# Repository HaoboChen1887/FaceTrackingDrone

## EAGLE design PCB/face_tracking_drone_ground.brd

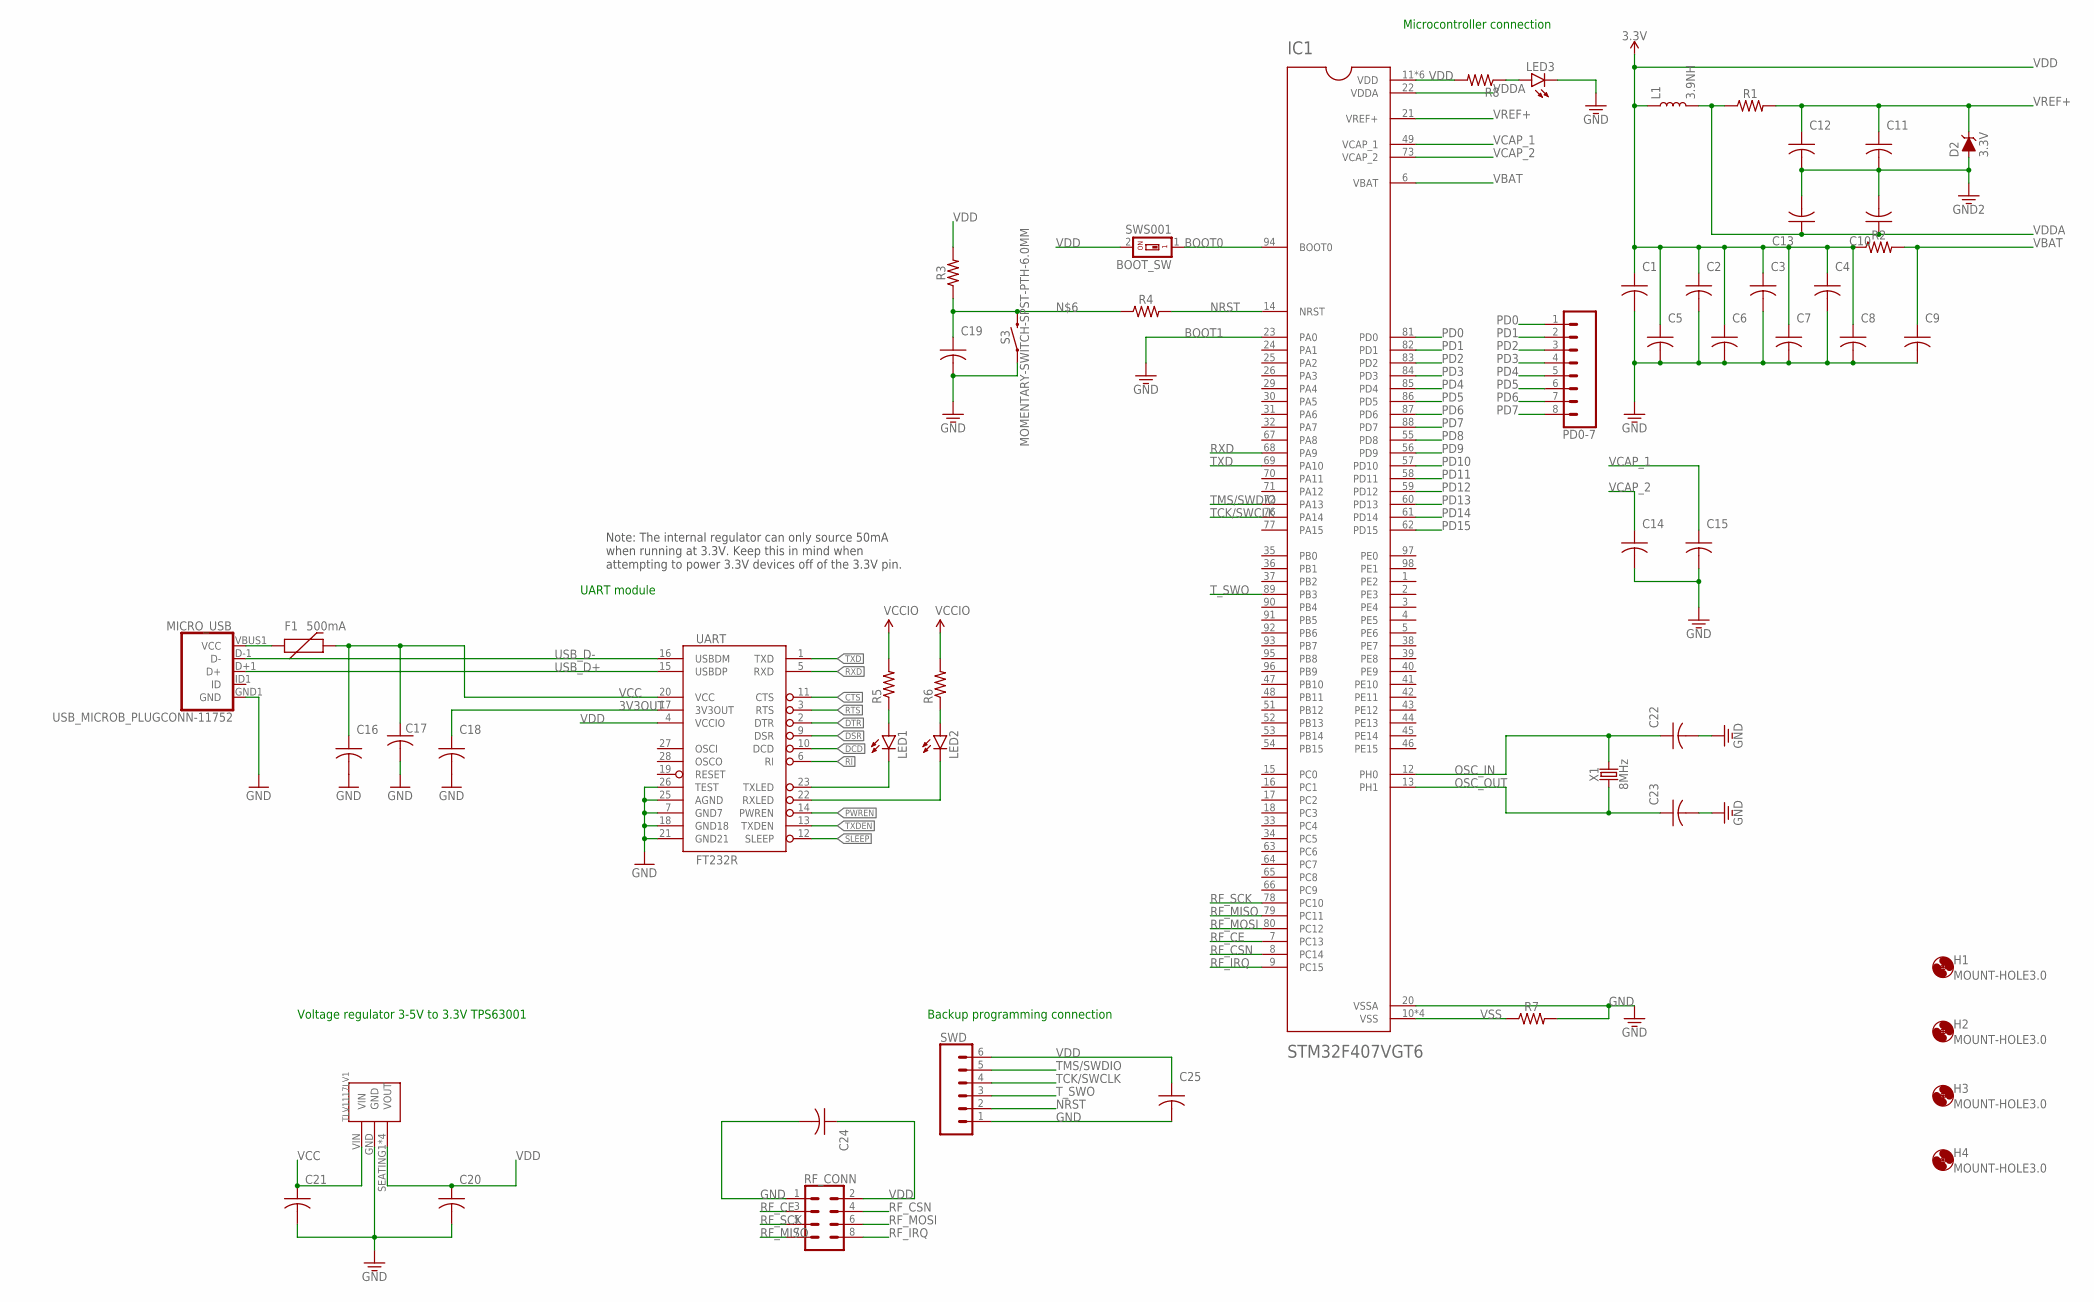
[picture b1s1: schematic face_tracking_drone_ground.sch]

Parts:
BOOT_SW: SWS001; SMS-001
C1, C2, C3, C4, C5, C6, C7, C8, C9, C10, C11, C16, C18, C20, C21, C24, C25: 0.1uF; C0805
C12, C13: 1uF; C0805
C14, C15, C19: 2.2uF; C0805
C17: 10uF; C0805
C22, C23: 20pF; C0805
D2: 3.3V; SOD-323
F1: 500mA; PTC-1206
H1, H2, H3, H4: MOUNT-HOLE3.0; 3,0
IC1: STM32F407VGT6; QFP50P1600X1600X160-100N
L1: 3.9NH; 0402
LED1: Red; SML0805
LED2, LED3: Green; SML0805
MICRO_USB: USB_MICROB_PLUGCONN-11752; USB-B-MICRO-SMD_V03
PD0-7: CONN_08"; 1X08
R1, R2, R3, R4, R5, R6, R8: M0805
R7: 0805
RF_CONN: CONN_04X2; 2X4
S3: MOMENTARY-SWITCH-SPST-PTH-6.0MM; TACTILE_SWITCH_PTH_6.0MM
SWD: CONN_06SILK_FEMALE_PTH; 1X06
TLV1117LV1: TLV1117LV33DCYR
UART: FT232R; SSOP28DB
X1: 8MHz; HC49U

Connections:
3V3OUT: C18.1, UART.17 (3V3OUT)
BOOT0: BOOT_SW.1, IC1.94 (BOOT0)
BOOT1: IC1.23 (PA0)
CTS: UART.11 (CTS)
DCD: UART.10 (DCD)
DSR: UART.9 (DSR)
DTR: UART.2 (DTR)
GND: C1.2, C2.2, C3.2, C4.2, C5.2, C6.2, C7.2, C8.2, C9.2, C10.2, C11.2, C12.2, C13.2, C14.2, C15.2, C16.2, C17.2, C18.2, C19.2, C20.2, C21.2, C22.2, C23.2, C24.2, C25.2, D2.A, IC1.20 (VSSA), LED3.C, MICRO_USB.GND1 (GND), R7.2, RF_CONN.1, S3.1, SWD.1, TLV1117LV1.GND, UART.7 (GND7), UART.18 (GND18), UART.21 (GND21), UART.25 (AGND), UART.26 (TEST)
unnamed: LED1.A, R5.1
unnamed: LED3.A, R8.1
unnamed: LED2.A, R6.1
unnamed: F1.1, MICRO_USB.VBUS1 (VCC)
unnamed: C19.1, R3.1, R4.1, S3.3 (2)
NRST: IC1.14 (NRST), R4.2, SWD.2
OSC_IN: C22.1, IC1.12 (PH0), X1.2
OSC_OUT: C23.1, IC1.13 (PH1), X1.1
PD0: IC1.81 (PD0), PD0-7.1
PD1: IC1.82 (PD1), PD0-7.2
PD2: IC1.83 (PD2), PD0-7.3
PD3: IC1.84 (PD3), PD0-7.4
PD4: IC1.85 (PD4), PD0-7.5
PD5: IC1.86 (PD5), PD0-7.6
PD6: IC1.87 (PD6), PD0-7.7
PD7: IC1.88 (PD7), PD0-7.8
PD8: IC1.55 (PD8)
PD9: IC1.56 (PD9)
PD10: IC1.57 (PD10)
PD11: IC1.58 (PD11)
PD12: IC1.59 (PD12)
PD13: IC1.60 (PD13)
PD14: IC1.61 (PD14)
PD15: IC1.62 (PD15)
PWREN: UART.14 (PWREN)
RF_CE: IC1.7 (PC13), RF_CONN.3
RF_CSN: IC1.8 (PC14), RF_CONN.4
RF_IRQ: IC1.9 (PC15), RF_CONN.8
RF_MISO: IC1.79 (PC11), RF_CONN.7
RF_MOSI: IC1.80 (PC12), RF_CONN.6
RF_SCK: IC1.78 (PC10), RF_CONN.5
RI: UART.6 (RI)
RTS: UART.3 (RTS)
RXD: IC1.68 (PA9), UART.5 (RXD)
RXLED: LED2.C, UART.22 (RXLED)
SLEEP: UART.12 (SLEEP)
TCK/SWCLK: IC1.76 (PA14), SWD.4
TMS/SWDIO: IC1.72 (PA13), SWD.5
TXD: IC1.69 (PA10), UART.1 (TXD)
TXDEN: UART.13 (TXDEN)
TXLED: LED1.C, UART.23 (TXLED)
T_SWO: IC1.89 (PB3), SWD.3
USB_D+: MICRO_USB.D+1 (D+), UART.15 (USBDP)
USB_D-: MICRO_USB.D-1 (D-), UART.16 (USBDM)
VBAT: C9.1, IC1.6 (VBAT), R2.2
VCAP_1: C15.1, IC1.49 (VCAP_1)
VCAP_2: C14.1, IC1.73 (VCAP_2)
VCC: C16.1, C17.1, C21.1, F1.2, TLV1117LV1.VIN, UART.20 (VCC)
VCCIO: R5.2, R6.2
VDD: BOOT_SW.2, C1.1, C2.1, C3.1, C4.1, C5.1, C6.1, C7.1, C8.1, C20.1, C24.1, C25.1, IC1.11 (VDD), IC1.19 (VDD), IC1.28 (VDD), IC1.50 (VDD), IC1.75 (VDD), IC1.100 (VDD), L1.1, R2.1, R3.2, R8.2, RF_CONN.2, SWD.6, TLV1117LV1.SEATING1 (VOUT), TLV1117LV1.SEATING2 (VOUT), TLV1117LV1.SEATING3 (VOUT), TLV1117LV1.VOUT, UART.4 (VCCIO)
VDDA: C10.1, C13.1, IC1.22 (VDDA), L1.2, R1.1
VREF+: C11.1, C12.1, D2.C, IC1.21 (VREF+), R1.2
VSS: IC1.10 (VSS), IC1.27 (VSS), IC1.74 (VSS), IC1.99 (VSS), R7.1

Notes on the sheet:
Microcontroller connection
Voltage regulator 3-5V to 3.3V TPS63001
Note: The internal regulator can only source 50mA when running at 3.3V. Keep this in mind when attempting to power 3.3V devices off of the 3.3V pin.
UART module
Backup programming connection

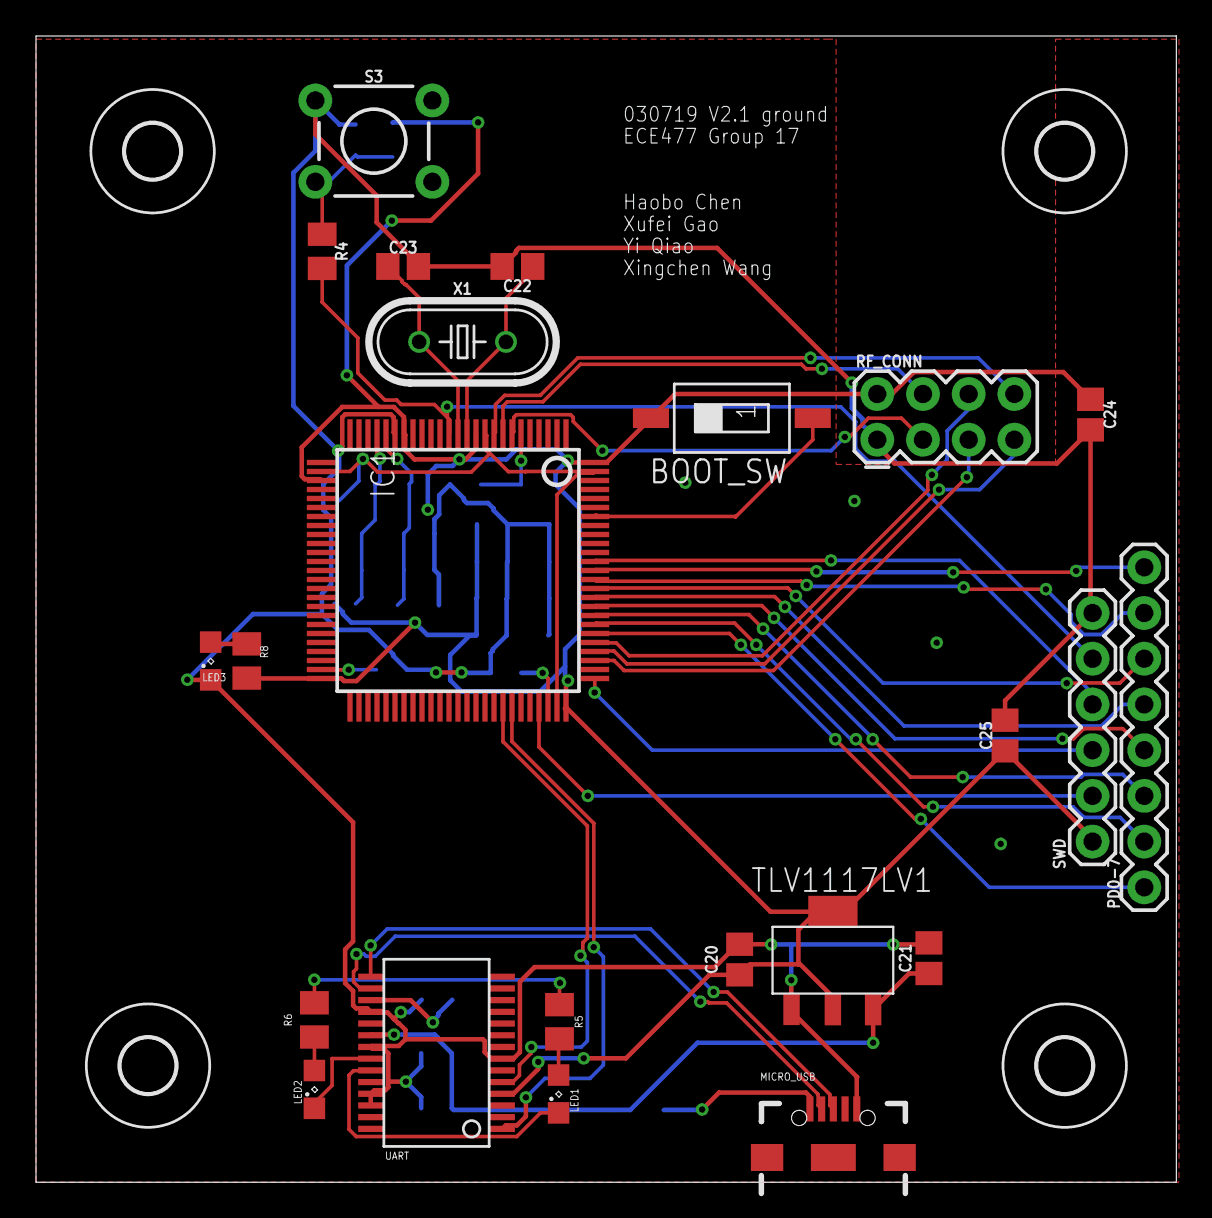
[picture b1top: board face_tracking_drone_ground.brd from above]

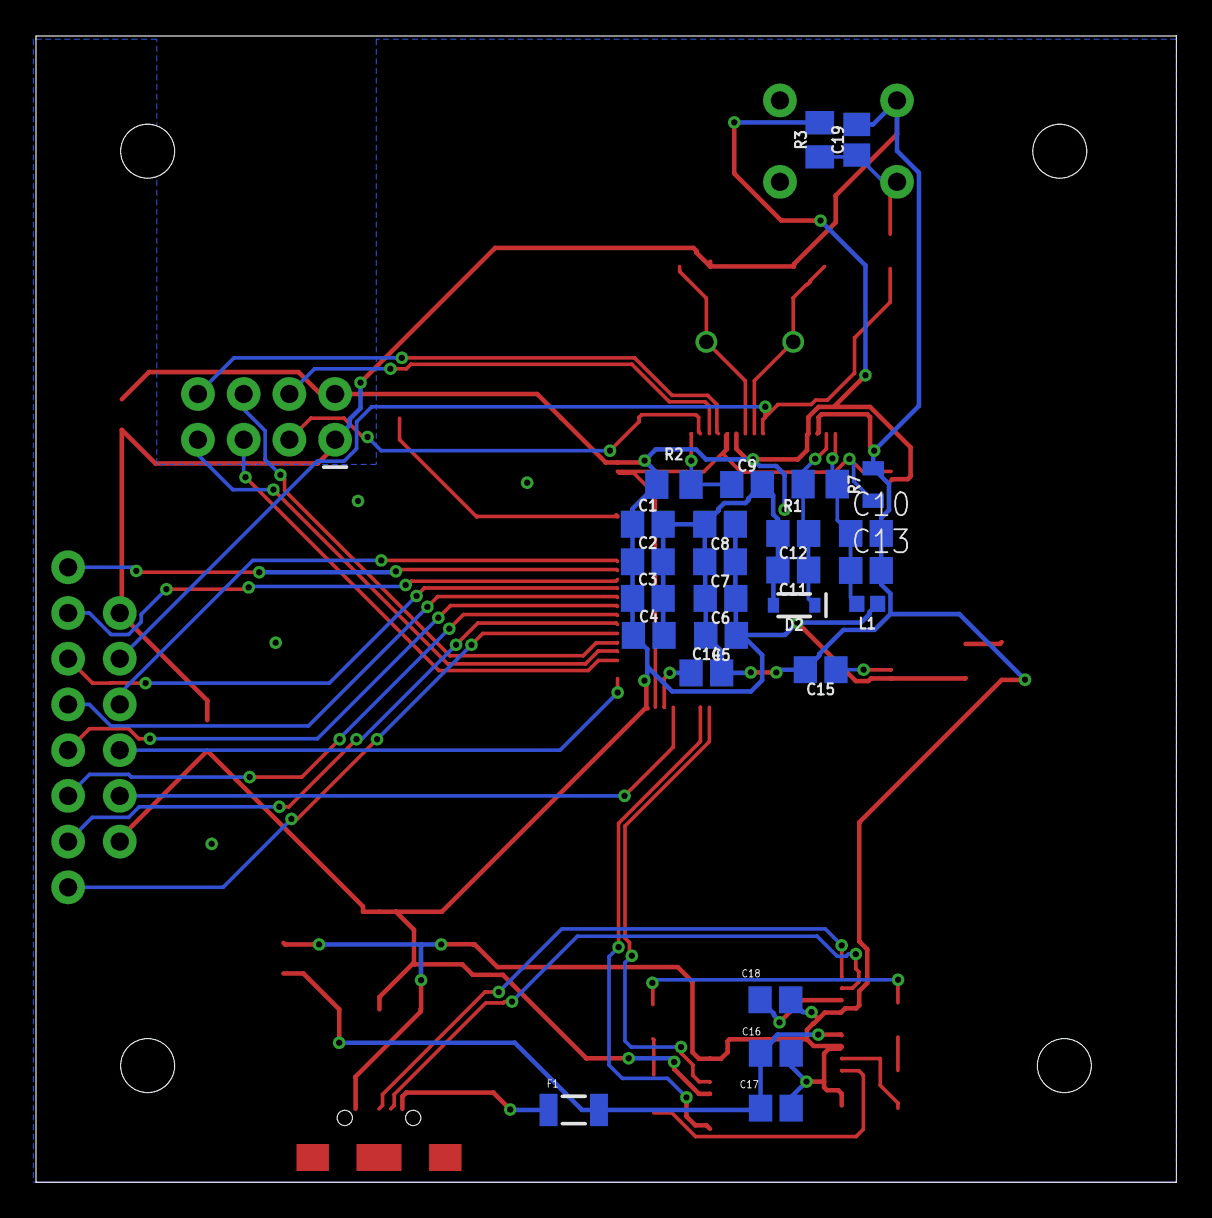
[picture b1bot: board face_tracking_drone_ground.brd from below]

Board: 2 copper layers, 63.4 x 63.7 mm, 53 parts (26 on the bottom side), 43 nets.

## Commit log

2020-08-21 reorganized

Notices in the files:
parts and their libraries:
SparkFun-Connectors: Licensing: Creative Commons ShareAlike 4.0 International - https://creativecommons.org/licenses/by-sa/4.0
SparkFun-Connectors: Licensing: CC v3.0 Share-Alike You are welcome to use this library for commercial purposes.
